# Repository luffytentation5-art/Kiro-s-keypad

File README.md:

Kiro's hackpad this hackpad has interesting features which include: RGBs,4 keys which you can modify, the case which for me is beutifull 
Cad MODEL:

Made in fusion
PCB
Here is the pcb and schemethic i made 

BOM 
4 SW_Push
Xiao-RP2040-DIP
2 SK6812MINI-E

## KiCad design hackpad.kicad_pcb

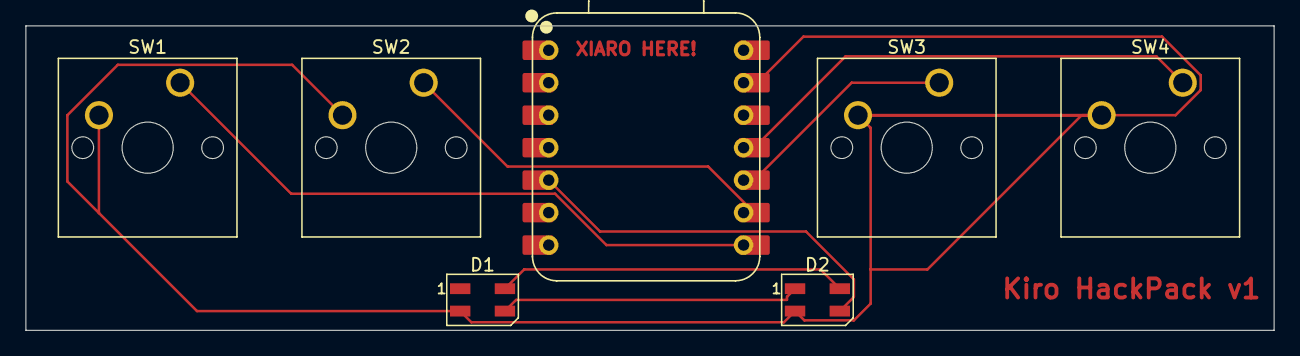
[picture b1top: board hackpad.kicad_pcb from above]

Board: 2 copper layers, 97.6 x 23.8 mm, 7 parts (0 on the bottom side), 8 nets.

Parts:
D1, D2: SK6812MINI; LED_SK6812MINI_PLCC4_3.5x3.5mm_P1.75mm
SW1, SW2, SW3, SW4: SW_Push; SW_Cherry_MX_1.00u_PCB
U1: XIAO-RP2040-DIP

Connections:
+5V: D1.4 (VDD), D2.4 (VDD)
GND: D1.2 (VSS), D2.2 (VSS), SW1.2, SW2.2, SW3.2, SW4.2, U1.13 (GND)
unnamed: D1.3 (DIN), D2.1 (DOUT)
unnamed: D2.3 (DIN), U1.5 (GPIO6/SDA)
unnamed: SW1.1, U1.8 (GPIO1/RX)
unnamed: SW2.1, U1.9 (GPIO2/SCK)
unnamed: SW4.1, U1.11 (GPIO3/MOSI)
unnamed: SW3.1, U1.10 (GPIO4/MISO)
